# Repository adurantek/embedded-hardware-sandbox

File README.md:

# embedded-hardware-sandbox
My Embedded Systems and Hardware Design Sandbox

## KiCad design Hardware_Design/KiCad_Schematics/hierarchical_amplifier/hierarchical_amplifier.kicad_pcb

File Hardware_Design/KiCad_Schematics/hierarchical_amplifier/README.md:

# HIERARCHICAL AMPLIFIER

I designed this circuit to understand the logic behind BJT transistor design, comprehend how fundamental circuits like audio amplifiers are structured, and **learn the basics of hierarchical design**.

## Components

    1 BC547
    4 Resistors
    3 Capacitors (10 microfarads each)
    3 Screw Terminals

## Uses and Purposes of Components

I used the R1 and R2 resistors to provide a **stable voltage value** to the Base pin of the transistor (voltage-divider). The C2 and C3 capacitors placed at the AUDIO_IN and AUDIO_OUT pins function as **coupling capacitors**; they protect or isolate the alternating current (AC) from the direct current (DC), preventing signal distortions. The R4 resistor on the Emitter pin is used to prevent the heating transistor from drawing excessive current, and the parallel-connected C1 capacitor acts as a **Bypass capacitor**, allowing the signal to flow smoothly through the capacitor, thereby maximizing the **AC Voltage Gain** of the circuit.

### PCB Design

### 3D View

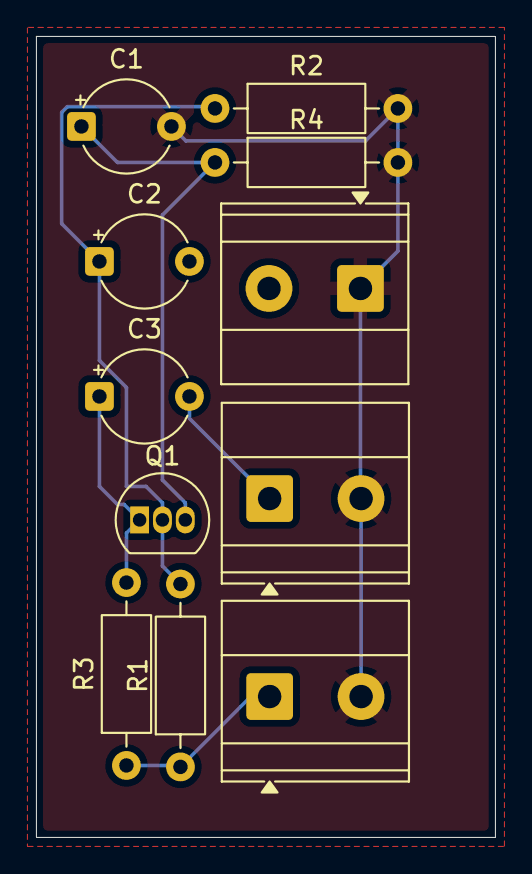
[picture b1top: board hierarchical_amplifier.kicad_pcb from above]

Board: 2 copper layers, 25.5 x 44.5 mm, 11 parts (0 on the bottom side), 6 nets.

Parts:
C1, C2, C3: 10uF; CP_Radial_Tantal_D5.0mm_P5.00mm
J1, J2, J3: Screw_Terminal_01x02; TerminalBlock_Phoenix_MKDS-1,5-2-5.08_1x02_P5.08mm_Horizont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
Q1: BC547; TO-92_Inline
R1: 47k; R_Axial_DIN0207_L6.3mm_D2.5mm_P10.16mm_Horizontal
R2: 10k; R_Axial_DIN0207_L6.3mm_D2.5mm_P10.16mm_Horizontal
R3: 4.7k; R_Axial_DIN0207_L6.3mm_D2.5mm_P10.16mm_Horizontal
R4: 1k; R_Axial_DIN0207_L6.3mm_D2.5mm_P10.16mm_Horizontal

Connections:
+12V: J3.1, R1.1, R3.1
/SesKuvvetlendirici/AUDIO_OUT: C3.2, J2.1
GND: C1.2, J1.1 (Pin_1_1), J2.2, J3.2, R2.2, R4.2
unnamed: C2.1, Q1.2 (B), R1.2, R2.1
unnamed: C3.1, Q1.1 (C), R3.2
unnamed: C1.1, Q1.3 (E), R4.1

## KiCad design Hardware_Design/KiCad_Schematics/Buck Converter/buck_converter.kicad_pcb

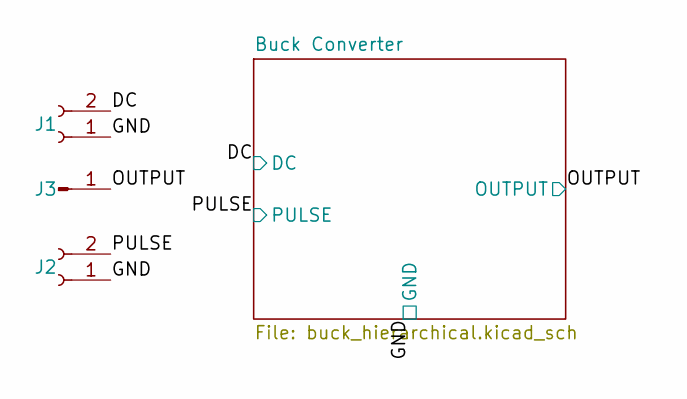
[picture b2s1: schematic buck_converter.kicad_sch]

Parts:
J1, J2: Conn_01x02_Socket; PinSocket_1x02_P2.54mm_Vertical
J3: Conn_01x01_Pin; PinHeader_1x01_P2.54mm_Vertical

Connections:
/DC: J1.2; also elsewhere on the board
/GND: J1.1, J2.1; also elsewhere on the board
/OUTPUT: J3.1 (Pin_1_1); also elsewhere on the board
/PULSE: J2.2; also elsewhere on the board

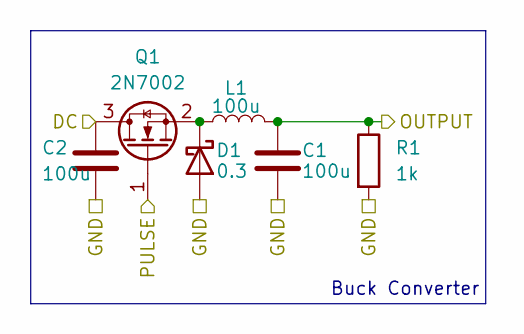
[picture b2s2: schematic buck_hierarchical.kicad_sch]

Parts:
C1, C2: 100u; CP_Radial_D4.0mm_P1.50mm
D1: 0.3; D_A-405_P7.62mm_Horizontal
L1: 100u; L_Radial_D6.0mm_P4.00mm
Q1: 2N7002; TO-220-3_Vertical
R1: 1k; R_Axial_DIN0204_L3.6mm_D1.6mm_P5.08mm_Horizontal

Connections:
/DC: C2.1, Q1.3 (D); also elsewhere on the board
/GND: C1.2, C2.2, D1.2 (A), R1.2; also elsewhere on the board
/OUTPUT: C1.1, L1.2, R1.1; also elsewhere on the board
/PULSE: Q1.1 (G); also elsewhere on the board
unnamed: D1.1 (K), L1.1, Q1.2 (S)

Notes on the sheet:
Buck Converter

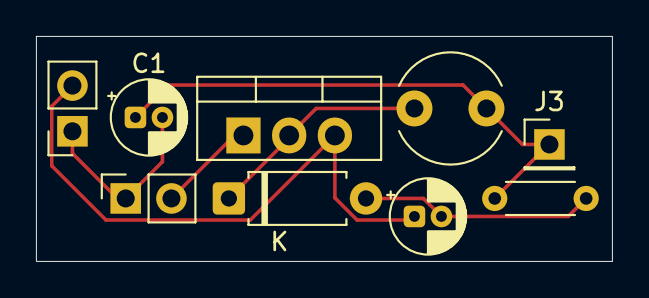
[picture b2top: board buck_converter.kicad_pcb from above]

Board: 2 copper layers, 32.0 x 12.5 mm, 9 parts (0 on the bottom side), 5 nets.

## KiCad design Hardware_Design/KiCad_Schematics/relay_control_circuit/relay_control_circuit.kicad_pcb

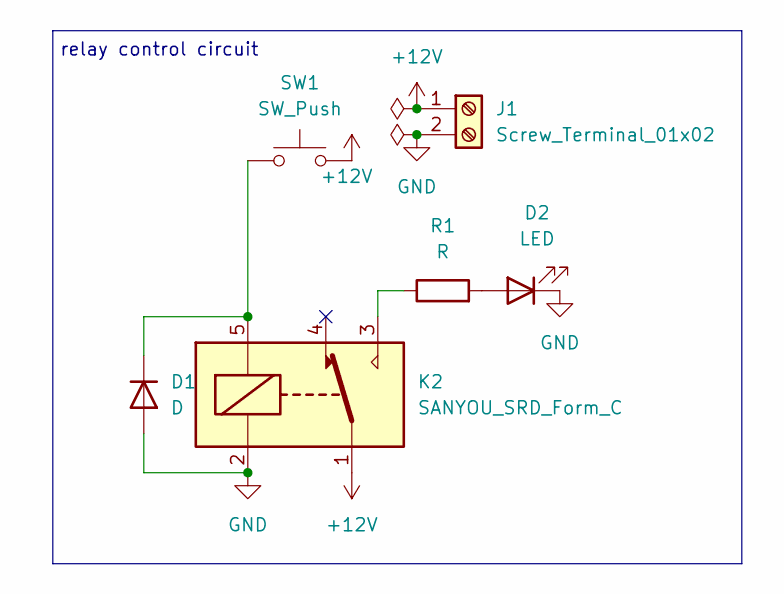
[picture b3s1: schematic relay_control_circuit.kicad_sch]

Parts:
D1: D; D_DO-41_SOD81_P10.16mm_Horizontal
D2: LED; LED_D5.0mm
J1: Screw_Terminal_01x02; TerminalBlock_Phoenix_MKDS-1,5-2-5.08_1x02_P5.08mm_Horizont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
K2: SANYOU_SRD_Form_C; Relay_SPDT_SANYOU_SRD_Series_Form_C
R1: R; R_Axial_DIN0207_L6.3mm_D2.5mm_P10.16mm_Horizontal
SW1: SW_Push; SW_PUSH_6mm

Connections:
+12V: J1.1, K2.1, SW1.2
GND: D1.2 (A), D2.1 (K), J1.2, K2.2
unnamed: D1.1 (K), K2.5, SW1.1
unnamed: D2.2 (A), R1.2
unnamed: K2.3, R1.1

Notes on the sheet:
relay control circuit

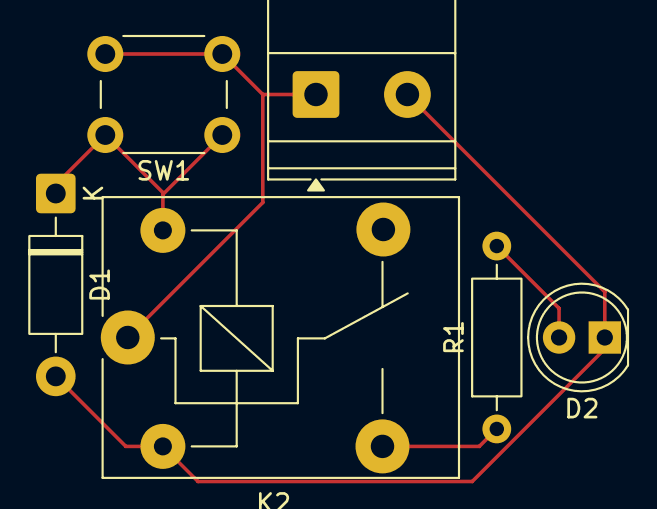
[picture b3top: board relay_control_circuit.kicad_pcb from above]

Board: 2 copper layers, 6 parts (0 on the bottom side), 5 nets.

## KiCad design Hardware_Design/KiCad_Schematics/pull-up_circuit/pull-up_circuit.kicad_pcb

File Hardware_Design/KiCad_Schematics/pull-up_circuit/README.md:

# PULL-UP CIRCUIT

## Purpose

I designed this circuit to understand the logic of pull-up resistors and why we use them.

## Learning Outcomes

- ✅ Pull-up design rules were learned
- ✅ It was understood that pull-up resistors must be used in designs to prevent **floating** at microcontroller pin inputs or similar scenarios.

## Technical Details

### Circuit Design

- Components list

    **2x 1x1 Connectors (J2, J3)**
    
    **2x 330Ω Resistors (R3, R4)**

    **1x LED Diode**

    **1x Push Button (SW2)**

- Design calculations

Taking the VCC voltage as a 5V reference.

**R4 value selected for the safe operation of the LED:** $$I_{LED} = \frac{V_{CC} - V_f}{R_4} = \frac{5\text{V} - 2\text{V}}{330\,\Omega} \approx 9.09\text{ mA}$$

**Power dissipation value on the R3 resistor:**

$$P = \frac{V_{CC}^2}{R_3} = \frac{5^2}{330} \approx 75\text{ mW}$$

- Schematic explanation

    In the circuit, if we consider the J3 connector as the test point where the digital input signal is applied and the J2 connector as the microcontroller pin, the digital value from J3 is directly tied to J2. This ensures a constant digital '1' state, eliminates noise, and prevents the **pin from floating**. When the SW2 switch is activated, it connects the line directly to ground, pulling the digital value down to '0'. In this way, **floating** is completely prevented.

### Simulation/Testing

- Test results

    Case 1: BUTTON RELEASED -> Logic value 1, J2 connector senses VCC.
    
    Case 2: BUTTON PRESSED -> Logic value 0, J2 connector is connected to ground.

- Images

## Design Decisions

Resistors R3 and R4 were placed to prevent short circuits and limit current, the push button was utilized to simulate the pull-up mechanism, and the LED was included for visual status control.

## Future Improvements

- Adding a capacitor ($C$) in parallel with the button to prevent mechanical contact bounce (signal sparking) at the hardware level.

- Adding an NPN transistor driver to eliminate the voltage drop caused by the LED load. This ensures that the J2 pin stays at a full 5V instead of dropping to ~3.3V when the LED draws current.

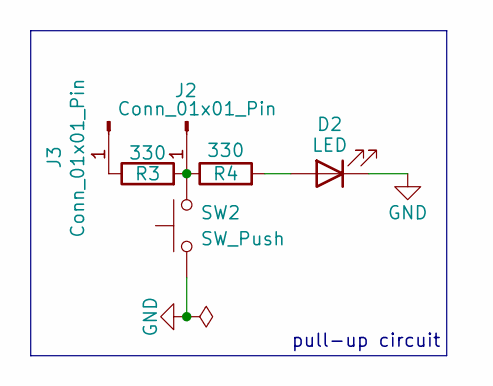
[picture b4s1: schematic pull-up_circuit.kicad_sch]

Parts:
D2: LED; LED_D1.8mm_W1.8mm_H2.4mm_Horizontal_O3.81mm_Z1.6mm
J2, J3: Conn_01x01_Pin; TerminalBlock_MetzConnect_360271_1x01_Horizontal_ScrewM3.0_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
R3, R4: 330; R_Axial_DIN0204_L3.6mm_D1.6mm_P5.08mm_Horizontal
SW2: SW_Push; SW_DIP_SPSTx01_Piano_10.8x4.1mm_W7.62mm_P2.54mm

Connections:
+3.3V: J3.1 (Pin_1_1), R3.1
GND: D2.1 (K), SW2.1
unnamed: D2.2 (A), R4.2
unnamed: J2.1 (Pin_1_1), R3.2, R4.1, SW2.2

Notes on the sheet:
pull-up circuit

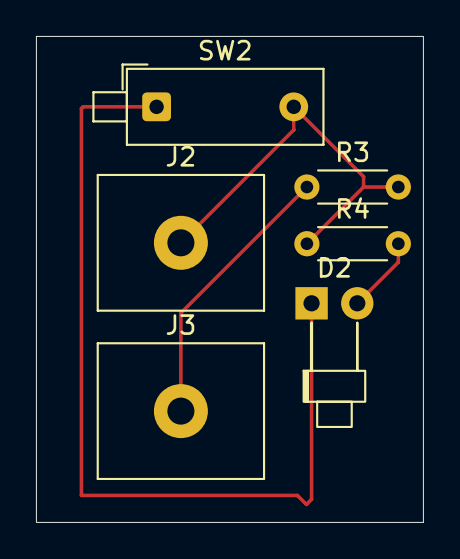
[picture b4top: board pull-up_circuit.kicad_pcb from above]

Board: 2 copper layers, 21.5 x 27.0 mm, 6 parts (0 on the bottom side), 4 nets.

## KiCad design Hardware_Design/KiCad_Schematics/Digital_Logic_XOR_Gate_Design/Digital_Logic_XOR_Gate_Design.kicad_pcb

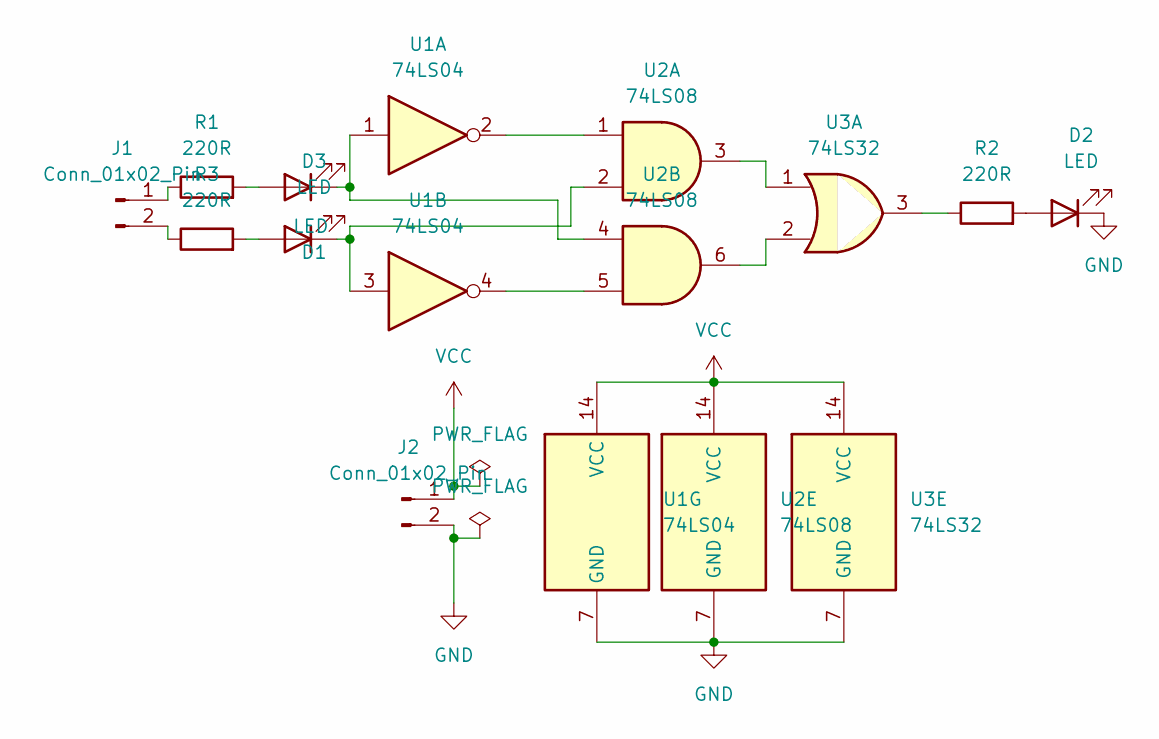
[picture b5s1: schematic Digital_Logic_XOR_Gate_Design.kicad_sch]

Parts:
D1, D2, D3: LED; LED_1206_3216Metric
J1, J2: Conn_01x02_Pin; PinHeader_1x02_P2.54mm_Vertical
R1, R2, R3: 220R; R_1206_3216Metric
U1: 74LS04; SOIC-14_3.9x8.7mm_P1.27mm
U2: 74LS08; SOIC-14_3.9x8.7mm_P1.27mm
U3: 74LS32; SOIC-14_3.9x8.7mm_P1.27mm

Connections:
GND: D2.1 (K), J2.2, U1.7 (GND), U2.7 (GND), U3.7 (GND)
unnamed: D1.2 (A), R1.2
unnamed: D1.1 (K), U1.1, U2.4
unnamed: D2.2 (A), R2.2
unnamed: D3.2 (A), R3.2
unnamed: D3.1 (K), U1.3, U2.2
unnamed: J1.1, R1.1
unnamed: J1.2, R3.1
unnamed: R2.1, U3.3
unnamed: U1.2, U2.1
unnamed: U1.4, U2.5
unnamed: U2.3, U3.1
unnamed: U2.6, U3.2
VCC: J2.1, U1.14 (VCC), U2.14 (VCC), U3.14 (VCC)

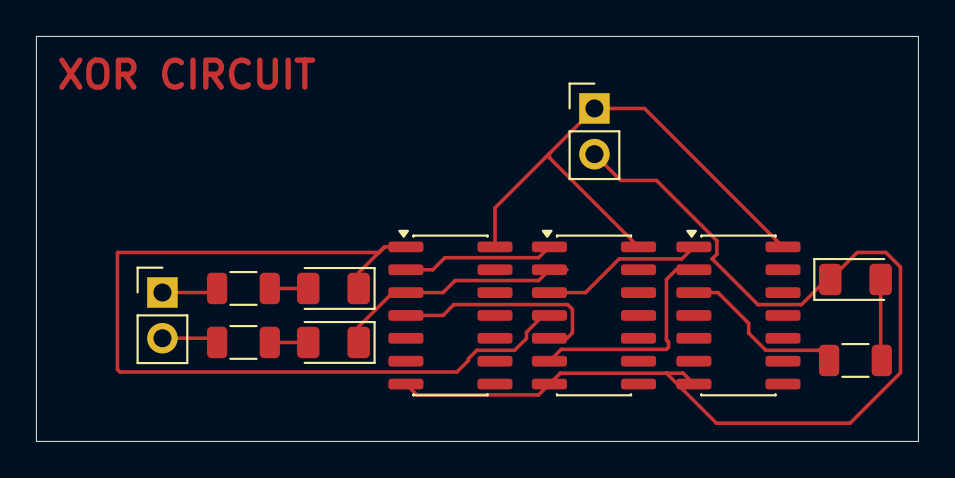
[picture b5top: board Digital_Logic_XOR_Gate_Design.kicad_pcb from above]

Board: 2 copper layers, 49.0 x 22.5 mm, 11 parts (0 on the bottom side), 14 nets.

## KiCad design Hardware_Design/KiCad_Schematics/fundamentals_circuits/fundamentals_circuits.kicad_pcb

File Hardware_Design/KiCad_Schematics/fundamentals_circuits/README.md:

# Fundamental Circuits

My goal with these circuits was to learn the **functions and behaviors** of basic components. Below I’ve explained what I did in each circuit, what I learned, and which behaviors I understood. To grasp the characteristics of each circuit – **especially for capacitors and inductors** – I also used KiCad’s simulation engine (powered by LTspice). 

## Current Divider

I designed this circuit to observe the behavior of current in **parallel-connected resistors**.

### Components

    2 Resistors
    1 1x2 Connector

## Voltage Divider

I designed this circuit to observe the behavior of voltage across **series-connected resistors**.

### Components

    2 Resistors
    1 1x2 Connector

## Half-Wave Rectifier

I designed this circuit to understand how we can pass **only the positive or only the negative half** of a sinusoidal signal.

### Components

    1 Diods
    1 Resistor
    1 1x2 Connector

## Full-Wave Rectifier

I designed and simulated this circuit to understand how to rectify **both the positive and negative halves** of a sinusoidal signal. This circuit especially helped me grasp the **relationship between current and diodes**. **A capacitor connected in parallel with the load resistor will smooth out the ripples.**

### Components

    4 Diods
    1 Resistor
    1 1x2 Connector

## RC Circuit

I designed and simulated this circuit to understand the behavior of a capacitor connected in series with a DC source: it initially acts like a short circuit while charging, and eventually behaves like an open circuit. Once the capacitor charges logarithmically (in **voltage**), it acts like an open circuit and no longer passes current.

### Components

    1 Capacitor
    1 Resistor
    1 1x2 Connector

## RL Circuit

I designed and simulated this circuit to understand the behavior of an inductor connected in series with a DC source: it initially acts like an open circuit, then charges and eventually behaves like a short circuit. Once the inductor charges logarithmically (in **current**), it acts like a short circuit and passes an infinite current (ideally).

### Components

    1 Inductor
    1 Resistor
    1 1x2 Connector

## PCB Designs

## 3D View

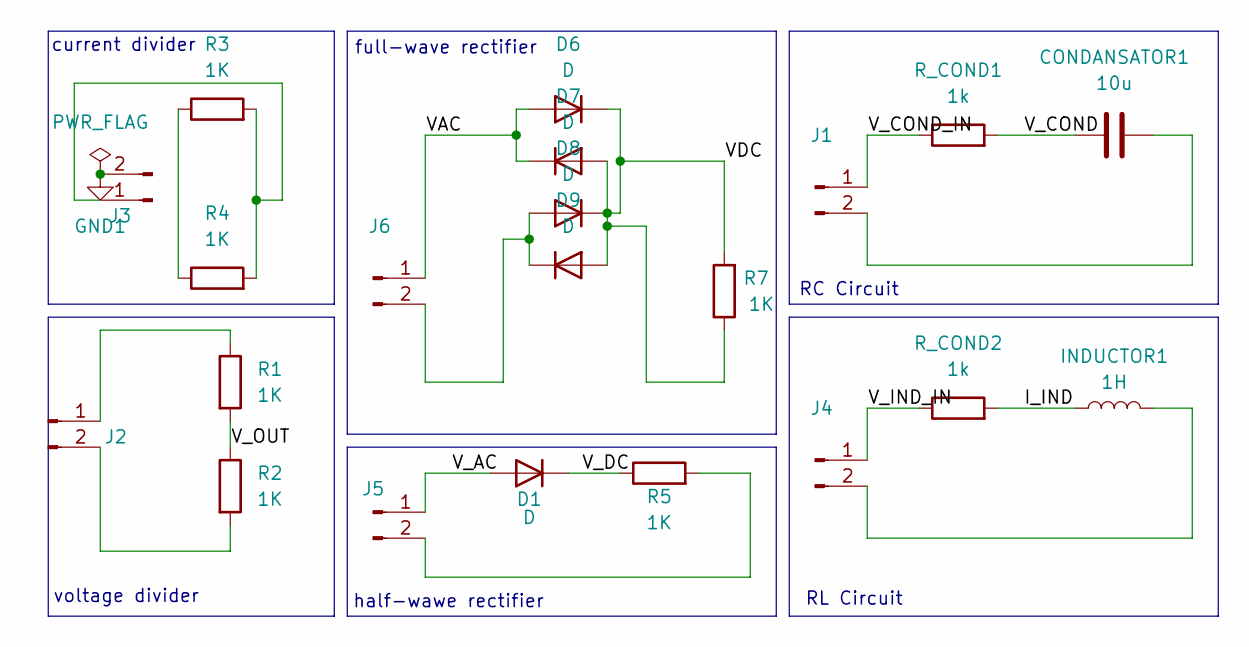
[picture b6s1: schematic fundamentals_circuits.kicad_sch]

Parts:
CONDANSATOR1: 10u; CP_Radial_D4.0mm_P1.50mm
D1, D6, D7, D8, D9: D; D_DO-34_SOD68_P2.54mm_Vertical_AnodeUp
INDUCTOR1: 1H; L_Axial_L7.0mm_D3.3mm_P2.54mm_Vertical_Fastron_MICC
J1, J2, J3, J4, J5, J6: Conn_01x02_Pin; PinHeader_1x02_P1.00mm_Vertical
R1, R2, R3, R4, R5, R7: 1K; R_Axial_DIN0204_L3.6mm_D1.6mm_P2.54mm_Vertical
R_COND1, R_COND2: 1k; R_Axial_DIN0204_L3.6mm_D1.6mm_P2.54mm_Vertical

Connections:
/I_IND: INDUCTOR1.1, R_COND2.2
/VAC: D6.2 (A), D7.1 (K), J6.1
/VDC: D6.1 (K), D7.2 (A), D8.1 (K), D9.2 (A), R7.1, R7.2
/V_AC: D1.2 (A), J5.1
/V_COND: CONDANSATOR1.1, R_COND1.2
/V_COND_IN: J1.1, R_COND1.1
/V_DC: D1.1 (K), R5.1
/V_IND_IN: J4.1, R_COND2.1
/V_OUT: R1.2, R2.1
GND1: J3.2
unnamed: D8.2 (A), D9.1 (K), J6.2
unnamed: CONDANSATOR1.2, J1.2
unnamed: J2.1, R1.1
unnamed: J2.2, R2.2
unnamed: J3.1, R3.2, R4.2
unnamed: INDUCTOR1.2, J4.2
unnamed: J5.2, R5.2
unnamed: R3.1, R4.1

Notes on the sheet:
voltage divider
half-wawe rectifier
full-wave rectifier
RC Circuit
RL Circuit
current divider

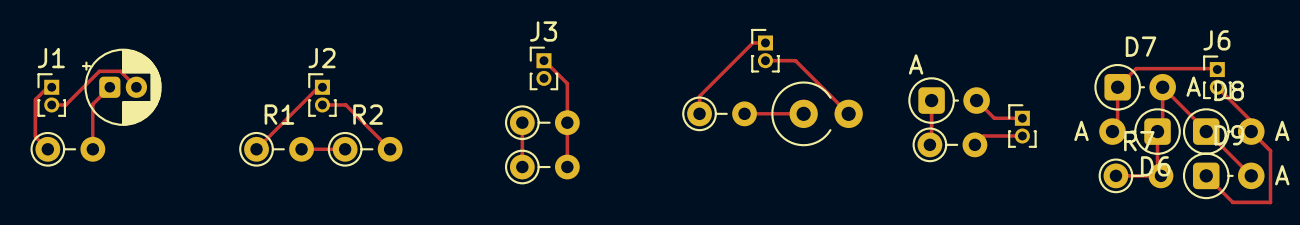
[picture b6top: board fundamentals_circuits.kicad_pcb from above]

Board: 2 copper layers, 21 parts (0 on the bottom side), 17 nets.

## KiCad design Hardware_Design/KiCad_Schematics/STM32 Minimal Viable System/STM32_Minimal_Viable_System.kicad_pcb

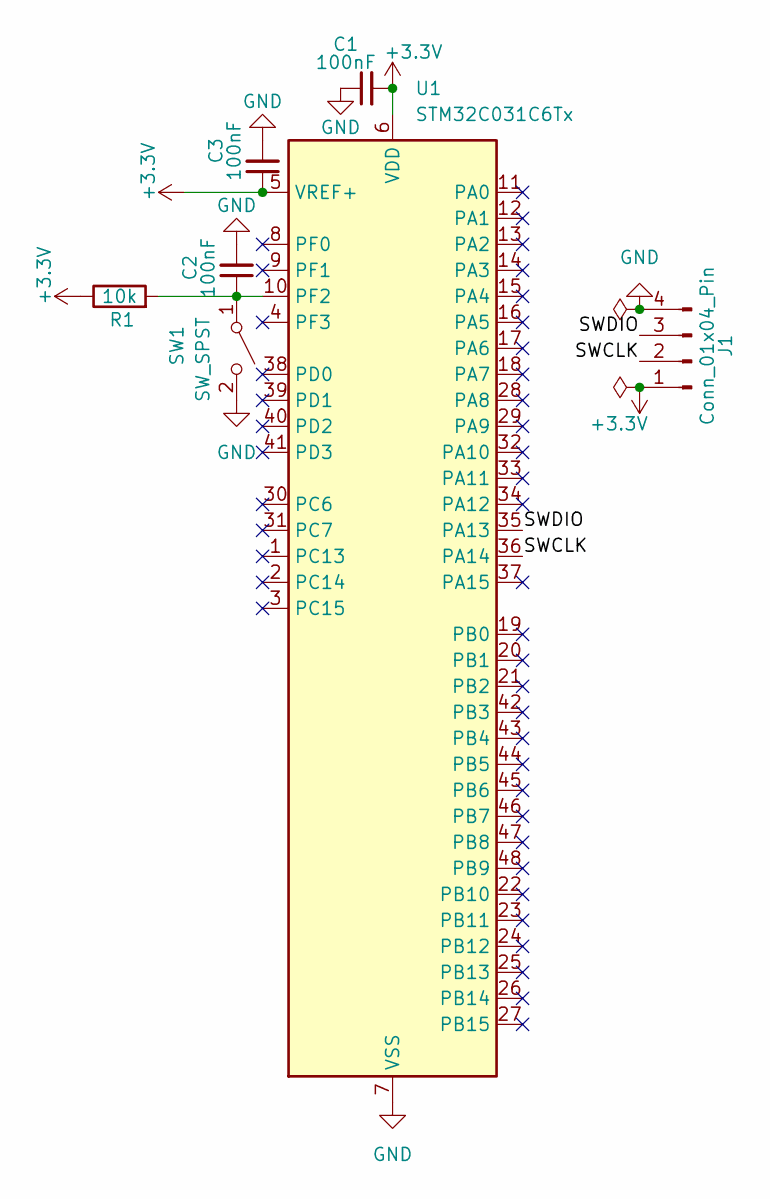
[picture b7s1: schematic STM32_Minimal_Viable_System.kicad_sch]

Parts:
C1, C2, C3: 100nF; CP_EIA-1608-08_AVX-J
J1: Conn_01x04_Pin; PinHeader_1x04_P2.00mm_Vertical
R1: 10k; R_0603_1608Metric
SW1: SW_SPST; SW_TH_Tactile_Omron_B3F-106x
U1: STM32C031C6Tx; LQFP-48_7x7mm_P0.5mm

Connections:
+3.3V: C1.2, C3.1, J1.1, R1.1, U1.5 (VREF+), U1.6 (VDD)
/SWCLK: J1.2, U1.36 (PA14)
/SWDIO: J1.3, U1.35 (PA13)
GND: C1.1, C2.2, C3.2, J1.4, SW1.2 (B), U1.7 (VSS)
unnamed: C2.1, R1.2, SW1.1 (A), U1.10 (PF2)

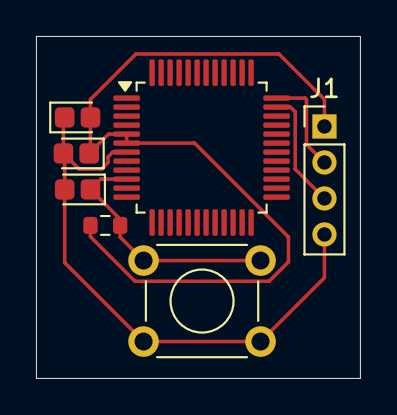
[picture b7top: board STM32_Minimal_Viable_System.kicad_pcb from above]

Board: 2 copper layers, 18.0 x 19.0 mm, 7 parts (0 on the bottom side), 5 nets.

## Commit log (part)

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2026-06-28 Added initial KiCad schematic practices
2026-06-28 Add C programming exercises and source files
2026-06-28 Add basic Arduino and STM32 exercises
